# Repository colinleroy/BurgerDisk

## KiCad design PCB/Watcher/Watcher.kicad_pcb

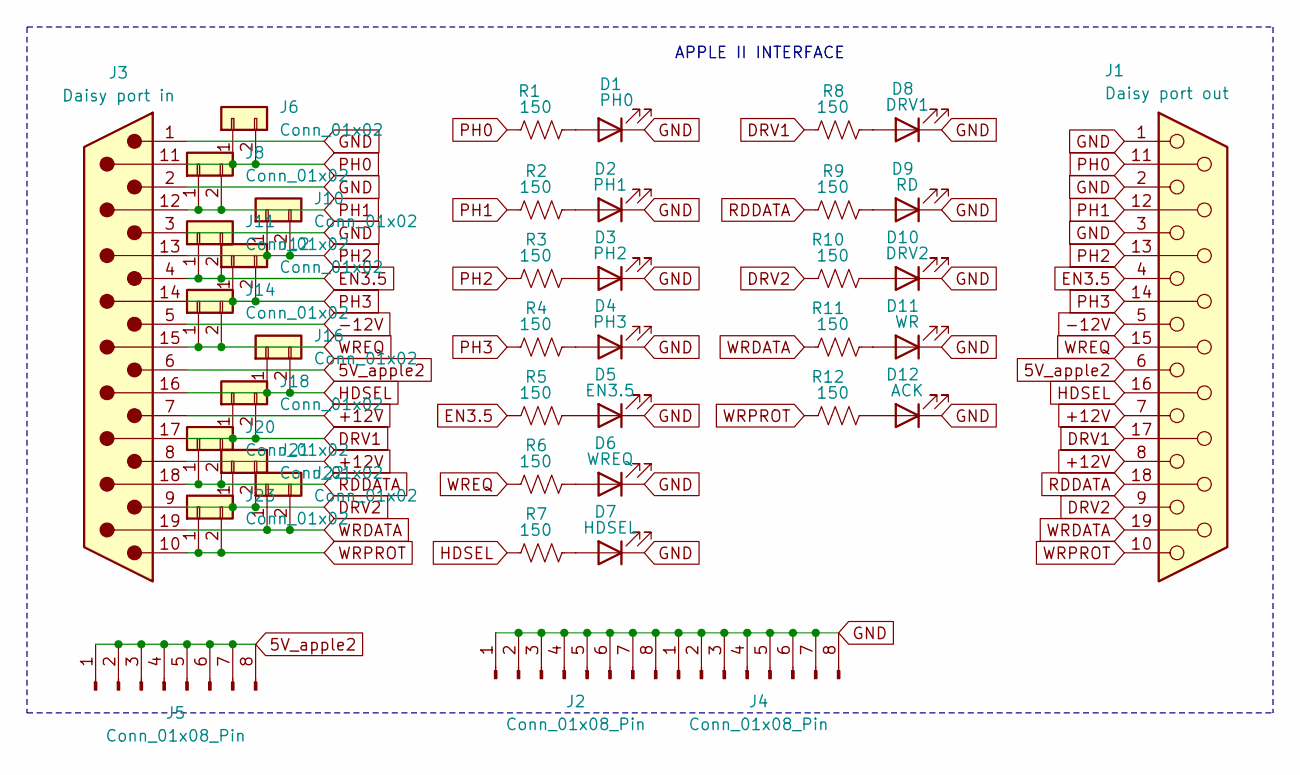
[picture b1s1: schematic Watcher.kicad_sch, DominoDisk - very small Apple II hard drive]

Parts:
D1: PH0; LED_0603_1608Metric; LCSC C2286
D2: PH1; LED_0603_1608Metric; LCSC C2286
D3: PH2; LED_0603_1608Metric; LCSC C2286
D4: PH3; LED_0603_1608Metric; LCSC C2286
D5: EN3.5; LED_0603_1608Metric; LCSC C2286
D6: WREQ; LED_0603_1608Metric; LCSC C2286
D7: HDSEL; LED_0603_1608Metric; LCSC C2286
D8: DRV1; LED_0603_1608Metric; LCSC C2286
D9: RD; LED_0603_1608Metric; LCSC C2286
D10: DRV2; LED_0603_1608Metric; LCSC C2286
D11: WR; LED_0603_1608Metric; LCSC C2286
D12: ACK; LED_0603_1608Metric; LCSC C2286
J1: Daisy port out; DSUB-19_Female_EdgeMount_Pitch2.77mm
J2, J4, J5: Conn_01x08_Pin; PinHeader_1x08_P1.00mm_Vertical
J3: Daisy port in; DSUB-19_Male_EdgeMount_Pitch2.77mm
J6, J8, J10, J11, J12, J14, J16, J18, J20, J21, J22, J23: Conn_01x02; PinHeader_1x02_P1.00mm_Vertical
R1, R2, R3, R4, R5, R6, R7, R8, R9, R10, R11, R12: 150; R_0603_1608Metric; LCSC C22808

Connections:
5V_apple2: J1.6, J3.6, J5.1, J5.2, J5.3, J5.4, J5.5, J5.6, J5.7, J5.8
+12V: J1.7, J1.8, J3.7, J3.8
-12V: J1.5, J3.5
DRV1: J1.17, J3.17, J18.1, J18.2, R8.1
DRV2: J1.9, J3.9, J21.1, J21.2, R10.1
EN3.5: J1.4, J3.4, J11.1, J11.2, R5.1
GND: D1.1 (K), D2.1 (K), D3.1 (K), D4.1 (K), D5.1 (K), D6.1 (K), D7.1 (K), D8.1 (K), D9.1 (K), D10.1 (K), D11.1 (K), D12.1 (K), J1.1, J1.2, J1.3, J2.1, J2.2, J2.3, J2.4, J2.5, J2.6, J2.7, J2.8, J3.1, J3.2, J3.3, J4.1, J4.2, J4.3, J4.4, J4.5, J4.6, J4.7, J4.8
HDSEL: J1.16, J3.16, J16.1, J16.2, R7.1
unnamed: D1.2 (A), R1.2
unnamed: D2.2 (A), R2.2
unnamed: D3.2 (A), R3.2
unnamed: D4.2 (A), R4.2
unnamed: D5.2 (A), R5.2
unnamed: D6.2 (A), R6.2
unnamed: D7.2 (A), R7.2
unnamed: D8.2 (A), R8.2
unnamed: D9.2 (A), R9.2
unnamed: D10.2 (A), R10.2
unnamed: D11.2 (A), R11.2
unnamed: D12.2 (A), R12.2
PH0: J1.11, J3.11, J6.1, J6.2, R1.1
PH1: J1.12, J3.12, J8.1, J8.2, R2.1
PH2: J1.13, J3.13, J10.1, J10.2, R3.1
PH3: J1.14, J3.14, J12.1, J12.2, R4.1
RDDATA: J1.18, J3.18, J20.1, J20.2, R9.1
WRDATA: J1.19, J3.19, J22.1, J22.2, R11.1
WREQ: J1.15, J3.15, J14.1, J14.2, R6.1
WRPROT: J1.10, J3.10, J23.1, J23.2, R12.1

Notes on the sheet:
APPLE II INTERFACE

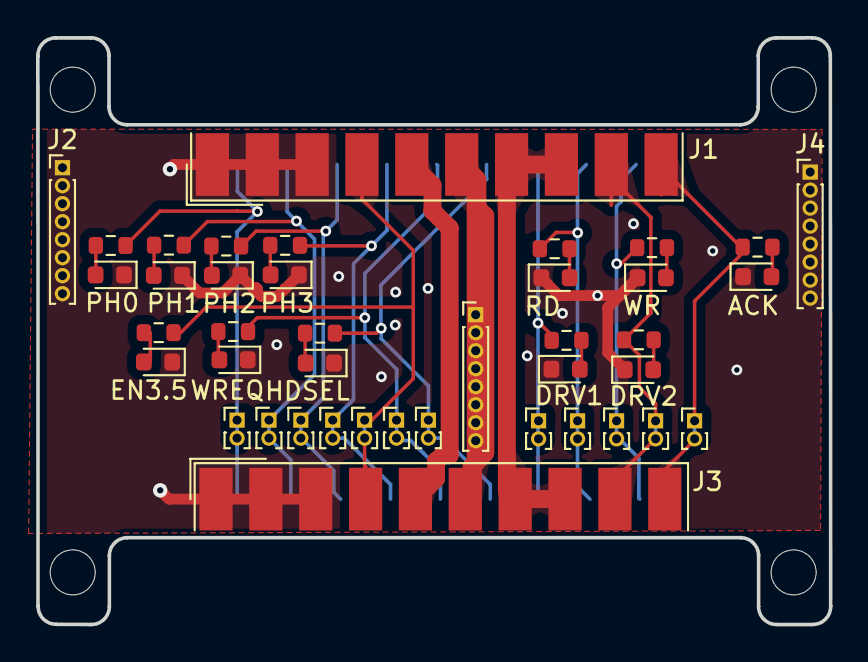
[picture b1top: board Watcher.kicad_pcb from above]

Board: 2 copper layers, 44.0 x 32.6 mm, 41 parts (0 on the bottom side), 28 nets.

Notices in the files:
PCB/Watcher/Watcher.kicad_sch:
License: CC BY-SA
